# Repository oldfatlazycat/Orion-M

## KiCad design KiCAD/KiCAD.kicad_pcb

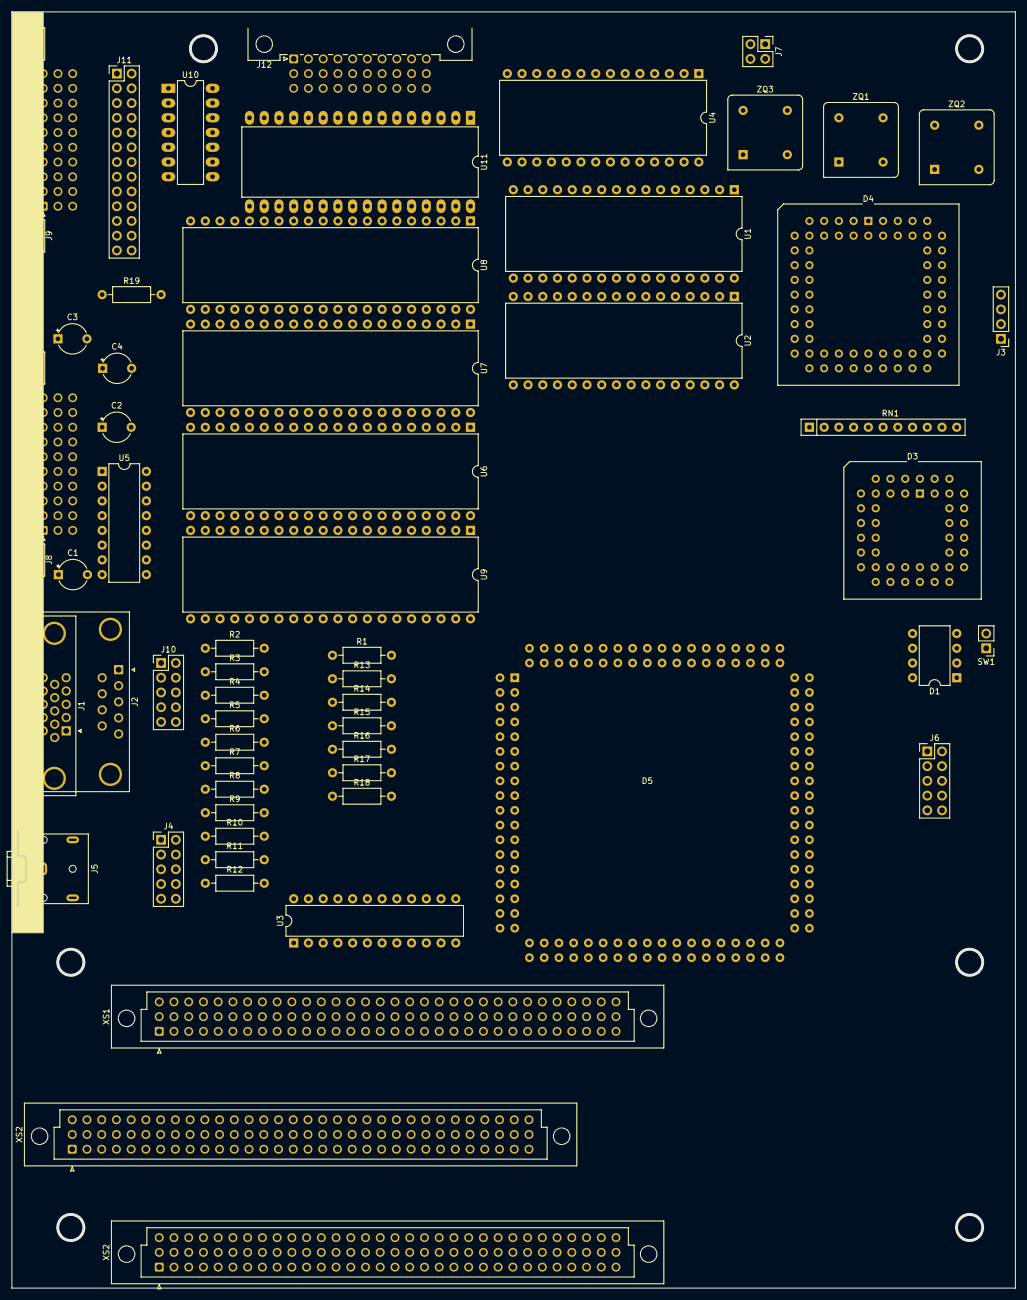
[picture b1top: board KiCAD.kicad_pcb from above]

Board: 2 copper layers, 173.0 x 220.0 mm, 58 parts (0 on the bottom side), 197 nets, no tracks yet.

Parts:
C1, C2, C4: 1mk; CP_Radial_Tantal_D5.0mm_P5.00mm
C3: 1 mk; CP_Radial_Tantal_D5.0mm_P5.00mm
D1: DS1232; DIP-8_W7.62mm
D3: Z80CPU; PLCC-44_THT-Socket
D4: Z180; PLCC-68_THT-Socket
D5: ALTERA EPM3256; TQFP-DIP adapter
J1: VGA; DSUB-15-HD_Female_Horizontal_P2.29x1.98mm_EdgePinOffset3.03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
J2: RS232 9600/38400; DSUB-9_Male_Horizontal_P2.77x2.84mm_EdgePinOffset14.56mm_Ho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
J3: 28800/115200; PinHeader_1x04_P2.54mm_Vertical
J4: Conn_02x05_Odd_Even; PinHeader_2x05_P2.54mm_Vertical
J5: AudioJack3; Jack_3.5mm_CUI_SJ1-3523N_Horizontal
J6: JTAG; PinHeader_2x05_P2.54mm_Vertical
J7: ROM SEL; PinHeader_2x02_P2.54mm_Vertical
J8: Ext. Connector; DIN41612_R3_3x10_Male_Horizontal_THT
J9: Ext. Keyboard; DIN41612_R3_3x10_Male_Horizontal_THT
J10: COM1; PinHeader_2x05_P2.54mm_Vertical
J11: Int. Keyboard; PinHeader_2x13_P2.54mm_Vertical
J12: ROM DIsk; DIN41612_R3_3x10_Male_Horizontal_THT
R1: 10k; R_Axial_DIN0207_L6.3mm_D2.5mm_P10.16mm_Horizontal
R2, R7, R9: 330; R_Axial_DIN0207_L6.3mm_D2.5mm_P10.16mm_Horizontal
R3, R4, R6: 22k; R_Axial_DIN0207_L6.3mm_D2.5mm_P10.16mm_Horizontal
R5, R8, R10: 680; R_Axial_DIN0207_L6.3mm_D2.5mm_P10.16mm_Horizontal
R11, R12: 470; R_Axial_DIN0207_L6.3mm_D2.5mm_P10.16mm_Horizontal
R13, R16, R19: 1k; R_Axial_DIN0207_L6.3mm_D2.5mm_P10.16mm_Horizontal
R14, R15, R17, R18: 2.2k; R_Axial_DIN0207_L6.3mm_D2.5mm_P10.16mm_Horizontal
RN1: 10 x 10k; R_Array_SIP11
SW1: Reset; PinHeader_1x02_P2.54mm_Vertical
U1, U2: AS6C4008-55PCN; DIP-32_W15.24mm
U3: 74LS154; DIP-24_W7.62mm
U4: 27C64; DIP-28_W15.24mm
U5: MAX232; DIP-16_W7.62mm
U6, U7, U8: 82C55A; DIP-40_W15.24mm
U9: YM2149; DIP-40_W15.24mm
U10: 74HCT04; DIP-14_W7.62mm_LongPads
U11: 27C010; DIP-32_W15.24mm_LongPads
XS1, XS2, XS2#2: DIN41612 3x32 Vertical; DIN41612_C_3x32_Female_Vertical_THT
ZQ1: 15,36 MHZ; Oscillator_DIP-8
ZQ2: 1,8432 MHZ; Oscillator_DIP-8
ZQ3: 5,5296 MHZ; Oscillator_DIP-8

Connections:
+5V: C3.1, D1.2 (TD), D1.8 (Vcc), D3.11 (VCC), D4.34 (VCC), D5.24 (VCCIO), D5.50 (VCCIO), D5.51 (VCCINT), D5.58 (VCCINT), D5.73 (VCCIO), D5.76 (VCCIO), D5.95 (VCCIO), D5.115 (VCCIO), D5.123 (VCCINT), D5.130 (VCCINT), D5.144 (VCCIO), J3.4, J6.4, J8.c10, J9.c10, J12.c10, R1.1, RN1.1 (common), U1.32 (VCC), U2.32 (VCC), U3.24 (VCC), U4.28 (VCC), U5.16 (VCC), U6.26 (VCC), U7.26 (VCC), U8.26 (VCC), U9.40 (VCC), U11.32 (VCC), XS1.a27 (Vcc), XS1.b27 (Vcc), XS1.c27 (Vcc), XS2.a27 (Vcc), XS2.b27 (Vcc), XS2.c27 (Vcc), XS2#2.a27 (Vcc), XS2#2.b27 (Vcc), XS2#2.c27 (Vcc), ZQ1.8 (Vcc), ZQ2.8 (Vcc), ZQ3.8 (Vcc)
+12V: XS1.c2 (+12V), XS2.c2 (+12V), XS2#2.c2 (+12V)
-5V: XS1.b2 (-5V), XS2.b2 (-5V), XS2#2.b2 (-5V)
/A0: D3.30 (A0), D4.14 (A0), U1.12 (A0), U2.12 (A0), U4.10 (A0)
/A1: D3.31 (A1), D4.15 (A1), U1.11 (A1), U2.11 (A1), U4.9 (A1)
/A2: D3.32 (A2), D4.16 (A2), U1.10 (A2), U2.10 (A2), U4.8 (A2)
/A3: D3.33 (A3), D4.17 (A3), U1.9 (A3), U2.9 (A3), U4.7 (A3)
/A4: D3.34 (A4), D4.19 (A4), U1.8 (A4), U2.8 (A4), U4.6 (A4)
/A5: D3.35 (A5), D4.20 (A5), U1.7 (A5), U2.7 (A5), U4.5 (A5)
/A6: D3.36 (A6), D4.21 (A6), U1.6 (A6), U2.6 (A6), U4.4 (A6)
/A7: D3.37 (A7), D4.22 (A7), U1.5 (A7), U2.5 (A7), U4.3 (A7)
/A8: D3.38 (A8), D4.23 (A8), U1.27 (A8), U2.27 (A8), U4.25 (A8)
/A9: D3.39 (A9), D4.24 (A9), U1.26 (A9), U2.26 (A9), U4.24 (A9)
/A10: D3.40 (A10), D4.25 (A10), U1.23 (A10), U2.23 (A10), U4.21 (A10)
/A11: D3.1 (A11), D4.26 (A11), U1.25 (A11), U2.25 (A11)
/A12: D3.2 (A12), D4.27 (A12), U1.4 (A12), U2.4 (A12)
/A13: D3.3 (A13), D4.28 (A13), U1.28 (A13), U2.28 (A13)
/A14: D3.4 (A14), D4.29 (A14), U1.3 (A14), U2.3 (A14)
/A15: D3.5 (A15), D4.30 (A15), U1.31 (A15), U2.31 (A15)
/A16: D4.31 (A16), U1.2 (A16), U2.2 (A16)
/A17: D4.32 (A17), U1.30 (A17), U2.30 (A17)
/A18: D4.33 (A18), U1.1 (A18), U2.1 (A18)
/CTS: J2.8, J10.8, U5.8 (R2IN)
/D0: D3.14 (D0), D4.37 (D0), U1.13 (DQ0), U2.13 (DQ0), U4.11 (D0)
/D1: D3.15 (D1), D4.38 (D1), U1.14 (DQ1), U2.14 (DQ1), U4.12 (D1)
/D2: D3.12 (D2), D4.39 (D2), U1.15 (DQ2), U2.15 (DQ2), U4.13 (D2)
/D3: D3.8 (D3), D4.40 (D3), U1.17 (DQ3), U2.17 (DQ3), U4.15 (D3)
/D4: D3.7 (D4), D4.41 (D4), U1.18 (DQ4), U2.18 (DQ4), U4.16 (D4)
/D5: D3.9 (D5), D4.42 (D5), U1.19 (DQ5), U2.19 (DQ5), U4.17 (D5)
/D6: D3.10 (D6), D4.43 (D6), U1.20 (DQ6), U2.20 (DQ6), U4.18 (D6)
/D7: D3.13 (D7), D4.44 (D7), U1.21 (DQ7), U2.21 (DQ7), U4.19 (D7)
/EXTAL: D4.4 (EXTAL), ZQ1.5 (OUT)
/IO devices/A0: U6.9 (A0), U7.9 (A0), U8.9 (A0), U9.29 (BC1)
/IO devices/A1: U6.8 (A1), U7.8 (A1), U8.8 (A1), U9.28 (BC2)
/IO devices/A16: XS1.b21 (A16), XS2.b21 (A16), XS2#2.b21 (A16)
/IO devices/A17: XS1.b17 (A17), XS2.b17 (A17), XS2#2.b17 (A17)
/IO devices/A18: XS1.b18 (A18), XS2.b18 (A18), XS2#2.b18 (A18)
/IO devices/A19: XS1.b19 (A19), XS2.b19 (A19), XS2#2.b19 (A19)
/IO devices/CC_KEY: J9.c6, U6.12 (PC5)
/IO devices/D0: U6.34 (D0), U7.34 (D0), U8.34 (D0), U9.37 (DA0), XS1.b3 (D0), XS2.b3 (D0), XS2#2.b3 (D0)
/IO devices/D1: U6.33 (D1), U7.33 (D1), U8.33 (D1), U9.36 (DA1), XS1.c3 (D1), XS2.c3 (D1), XS2#2.c3 (D1)
/IO devices/D2: U6.32 (D2), U7.32 (D2), U8.32 (D2), U9.35 (DA2), XS1.b4 (D2), XS2.b4 (D2), XS2#2.b4 (D2)
/IO devices/D3: U6.31 (D3), U7.31 (D3), U8.31 (D3), U9.34 (DA3), XS1.c4 (D3), XS2.c4 (D3), XS2#2.c4 (D3)
/IO devices/D4: U6.30 (D4), U7.30 (D4), U8.30 (D4), U9.33 (DA4), XS1.b5 (D4), XS2.b5 (D4), XS2#2.b5 (D4)
/IO devices/D5: U6.29 (D5), U7.29 (D5), U8.29 (D5), U9.32 (DA5), XS1.c5 (D5), XS2.c5 (D5), XS2#2.c5 (D5)
/IO devices/D6: U6.28 (D6), U7.28 (D6), U8.28 (D6), U9.31 (DA6), XS1.b6 (D6), XS2.b6 (D6), XS2#2.b6 (D6)
/IO devices/D7: U6.27 (D7), U7.27 (D7), U8.27 (D7), U9.30 (DA7), XS1.c6 (D7), XS2.c6 (D7), XS2#2.c6 (D7)
/IO devices/RES: U6.35 (RESET), U7.35 (RESET), U8.35 (RESET), XS1.b20 (RESET), XS2.b20 (RESET), XS2#2.b20 (RESET)
/IO devices/RUS/LAT_KEY: J9.c8, U6.10 (PC7)
/IO devices/RUS/LAT_LED: U6.17 (PC3), U10.1
/IO devices/US_KEY: J9.c7, U6.11 (PC6)
/IO devices/~F700: U3.18 (E0), U3.19 (E1)
/IO devices/~RD: U6.5 (~RD), U7.5 (~RD), U8.5 (~RD), U9.27 (BDIR)
/IO devices/~WR: U6.36 (~WR), U7.36 (~WR), U8.36 (~WR)
/RTS: J2.7, J10.7, U5.14 (T1OUT)
/RXA1: D4.53 (RXA1), J3.3
/RxD: J2.2, J10.2, U5.13 (R1IN)
/TXA1: D4.51 (TXA1), J3.2
/TxD: J2.3, J10.3, U5.7 (T2OUT)
/~BUSRQ: D3.25 (~BUSRQ), D4.7 (~BUSRQ), RN1.7 (R6)
/~INT0: D4.10 (~INT0), RN1.4 (R3)
/~INT1: D4.11 (~INT1), RN1.5 (R4)
/~INT2: D3.16 (~INT), D4.12 (~INT2), RN1.6 (R5)
/~IORQ: D3.20 (~IORQ), D4.62 (~IORQ)
/~M1: D1.7 (~ST), D3.27 (~M1), D4.65 (~M1)
/~MREQ: D3.19 (~MREQ), D4.63 (~MREQ)
/~NMI: D3.17 (~NMI), D4.9 (~NMI), RN1.3 (R2)
/~RD: D3.21 (~RD), D4.67 (~RD), U1.24 (OE#), U2.24 (OE#), U4.22 (~OE)
/~RES: D1.6 (~RESET), D3.26 (~RESET), D4.8 (~RESET), RN1.2 (R1)
/~WAIT: D3.24 (~WAIT), D4.5 (~WAIT), RN1.8 (R7)
/~WR: D3.22 (~WR), D4.66 (~WR), U1.29 (WE#), U2.29 (WE#)
Earth: J6.2, J6.10
GND: C4.2, D1.3 (TOL), D1.4 (Vss), D3.29 (GND), D4.1 (GND), D4.2 (GND), D4.18 (GND), D4.36 (GND), D4.47 (~DCD0), D5.3 (GNDIO), D5.13 (GNDIO), D5.17 (GNDIO), D5.26 (GNDIO), D5.33 (GNDIO), D5.52 (GNDINT), D5.57 (GNDINT), D5.59 (GNDIO), D5.64 (GNDIO), D5.77 (GNDIO), D5.85 (GNDIO), D5.94 (GNDIO), D5.105 (GNDIO), D5.114 (GNDIO), D5.124 (GNDINT), D5.129 (GNDINT), D5.135 (GNDIO), J1.5, J1.6, J1.7, J1.8, J1.10, J2.5, J3.1, J4.2, J5.S, J7.1, J7.2, J8.a10, J9.a10, J10.5, J12.a10, R3.2, R4.2, R6.2, R17.2, R18.2, SW1.2, U1.16 (VSS), U2.16 (VSS), U3.12 (GND), U4.14 (GND), U5.15 (GND), U6.7 (GND), U7.7 (GND), U8.7 (GND), U9.1 (VSS), U11.1 (VPP), U11.16 (GND), U11.24 (~OE), U11.31 (~PGM), XS1.a15 (GND), XS1.b15 (GND), XS1.c15 (GND), XS2.a15 (GND), XS2.b15 (GND), XS2.c15 (GND), XS2#2.a15 (GND), XS2#2.b15 (GND), XS2#2.c15 (GND), ZQ1.4 (GND), ZQ2.4 (GND), ZQ3.4 (GND)
unnamed: D1.1 (~PBRST), SW1.1
unnamed: D4.50 (CKA0/~DREQ0), ZQ2.5 (OUT)
unnamed: D4.54 (CKA1/~TEND0), ZQ3.5 (OUT)
unnamed: D4.49 (RXA0), U5.12 (R1OUT)
unnamed: D4.48 (TXA0), U5.10 (T2IN)
unnamed: D4.46 (~CTS0), U5.9 (R2OUT)
unnamed: D4.45 (~RTS0), U5.11 (T1IN)
unnamed: D5.106 (IO_106), R5.1
unnamed: D5.107 (IO_107), R11.1
unnamed: D5.108 (IO_108), R12.1
unnamed: D5.109 (IO_109), R9.1
unnamed: D5.110 (IO_110), R7.1
unnamed: D5.111 (IO_111), R10.1
unnamed: D5.112 (IO_112), R8.1
unnamed: D5.113 (IO_113), R2.1
unnamed: D5.89 (TCK), J6.1
unnamed: D5.4 (TDI), J6.9
unnamed: D5.104 (TDO), J6.3
unnamed: D5.20 (TMS), J6.5
unnamed: J1.1, R2.2, R4.1, R10.2
unnamed: J1.2, R3.1, R8.2, R9.2
unnamed: J1.3, R5.2, R6.1, R7.2
unnamed: J1.13, R12.2
unnamed: J1.14, R11.2
unnamed: J4.5, R15.2, R16.2, R18.1
unnamed: J4.6, J5.R
unnamed: J4.9, R13.2, R14.2, R17.1
unnamed: J4.10, J5.T
unnamed: J7.3, RN1.10 (R9), U4.2 (A12)
unnamed: J7.4, RN1.11 (R10), U4.23 (A11)
unnamed: J9.c3, U10.2
unnamed: U3.1 (S0), XS1.a1 (~F70x)
unnamed: U3.2 (S1), XS1.a2 (~F71x)
unnamed: U3.3 (S2), XS1.a3 (~F72x)
unnamed: U3.4 (S3), XS1.a4 (~F73x)
unnamed: U3.5 (S4), XS1.a5 (~F74x)
unnamed: U3.6 (S5), XS1.a6 (~F75x)
unnamed: U3.7 (S6), XS1.a7 (~F76x)
unnamed: U3.8 (S7), XS1.a8 (~F77x)
unnamed: U3.9 (S8), XS1.a9 (~F78x)
unnamed: U3.10 (S9), XS1.a10 (~F79x)
unnamed: U3.11 (S10), XS1.a11 (~F7Ax)
unnamed: U3.13 (S11), XS1.a12 (~F7Bx)
unnamed: U3.14 (S12), XS1.a13 (~F7Cx)
unnamed: U3.15 (S13), XS1.a14 (~F7Dx)
unnamed: U3.16 (S14), XS1.a30 (NC)
unnamed: U3.17 (S15), XS1.a16 (~F7Fx)
unnamed: C1.1, U5.1 (C1+)
unnamed: C1.2, U5.3 (C1-)
unnamed: C2.1, U5.4 (C2+)
unnamed: C2.2, U5.5 (C2-)
unnamed: C3.2, U5.2 (VS+)
unnamed: C4.1, U5.6 (VS-)
unnamed: J9.a1, U6.4 (PA0)
unnamed: J9.a2, U6.3 (PA1)
unnamed: J9.a3, U6.2 (PA2)
unnamed: J9.a4, U6.1 (PA3)
unnamed: J9.a5, U6.40 (PA4)
unnamed: J9.a6, U6.39 (PA5)
unnamed: J9.a7, U6.38 (PA6)
unnamed: J9.a8, U6.37 (PA7)
unnamed: J9.b1, U6.18 (PB0)
unnamed: J9.b2, U6.19 (PB1)
unnamed: J9.b3, U6.20 (PB2)
unnamed: J9.b4, U6.21 (PB3)
unnamed: J9.b5, U6.22 (PB4)
unnamed: J9.b6, U6.23 (PB5)
unnamed: J9.b7, U6.24 (PB6)
unnamed: J9.b8, U6.25 (PB7)
unnamed: R19.1, U6.14 (PC0)
unnamed: J8.a1, U7.4 (PA0)
unnamed: J8.a2, U7.3 (PA1)
unnamed: J8.a3, U7.2 (PA2)
unnamed: J8.a4, U7.1 (PA3)
unnamed: J8.a5, U7.40 (PA4)
unnamed: J8.a6, U7.39 (PA5)
unnamed: J8.a7, U7.38 (PA6)
unnamed: J8.a8, U7.37 (PA7)
unnamed: J8.b1, U7.18 (PB0)
unnamed: J8.b2, U7.19 (PB1)
unnamed: J8.b3, U7.20 (PB2)
unnamed: J8.b4, U7.21 (PB3)
unnamed: J8.b5, U7.22 (PB4)
unnamed: J8.b6, U7.23 (PB5)
unnamed: J8.b7, U7.24 (PB6)
unnamed: J8.b8, U7.25 (PB7)
unnamed: J8.c1, U7.14 (PC0)
unnamed: J8.c2, U7.15 (PC1)
unnamed: J8.c3, U7.16 (PC2)
unnamed: J8.c4, U7.17 (PC3)
unnamed: J8.c5, U7.13 (PC4)
unnamed: J8.c6, U7.12 (PC5)
unnamed: J8.c7, U7.11 (PC6)
unnamed: J8.c8, U7.10 (PC7)
unnamed: R1.2, U9.25 (A8), U9.26 (~SEL)
unnamed: R13.1, U9.3 (A)
unnamed: R14.1, R15.1, U9.4 (B)
unnamed: R16.1, U9.38 (C)
unnamed: J12.b1, U8.18 (PB0), U11.12 (A0)
unnamed: J12.b2, U8.19 (PB1), U11.11 (A1)
unnamed: J12.b3, U8.20 (PB2), U11.10 (A2)
unnamed: J12.b4, U8.21 (PB3), U11.9 (A3)
unnamed: J12.b5, U8.22 (PB4), U11.8 (A4)
unnamed: J12.b6, U8.23 (PB5), U11.7 (A5)
unnamed: J12.b7, U8.24 (PB6), U11.6 (A6)
unnamed: J12.b8, U8.25 (PB7), U11.5 (A7)
unnamed: J12.c1, U8.14 (PC0), U11.27 (A8)
unnamed: J12.c2, U8.15 (PC1), U11.26 (A9)
unnamed: J12.c3, U8.16 (PC2), U11.23 (A10)
unnamed: J12.c4, U8.17 (PC3), U11.25 (A11)
unnamed: J12.c5, U8.13 (PC4), U11.4 (A12)
unnamed: J12.c6, U8.12 (PC5), U11.28 (A13)
unnamed: J12.c7, U8.11 (PC6), U11.29 (A14)
unnamed: J12.c8, U8.10 (PC7), U11.3 (A15)
unnamed: J9.c1, J12.b9, U6.15 (PC1), U11.2 (A16)
unnamed: J12.a1, U8.4 (PA0), U11.13 (D0)
unnamed: J12.a2, U8.3 (PA1), U11.14 (D1)
unnamed: J12.a3, U8.2 (PA2), U11.15 (D2)
unnamed: J12.a4, U8.1 (PA3), U11.17 (D3)
unnamed: J12.a5, U8.40 (PA4), U11.18 (D4)
unnamed: J12.a6, U8.39 (PA5), U11.19 (D5)
unnamed: J12.a7, U8.38 (PA6), U11.20 (D6)
unnamed: J12.a8, U8.37 (PA7), U11.21 (D7)
unnamed: J9.c2, J12.b10, U6.16 (PC2), U11.22 (~CE)
